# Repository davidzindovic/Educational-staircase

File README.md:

# Musical stairs with video effects
This project was constructed for use on the Faculty of Education, University of Ljubljana. The goal was to create attachable hardware to put onto an existing staircase (covering half the surface) with 2 turns and 25 steps.
Input data is processed by an ESP32, musical effects are played from an SD card with the help od MP3-TF player and visual effects are displayed on a projection/ screen via Raspberry Pi.
Data is transmitted from the ESP32 to RPI via Bluetooth.

# Hardware
- ESP32
- MP3-TF player module
- Mux 4051
- Raspberry Pi 5

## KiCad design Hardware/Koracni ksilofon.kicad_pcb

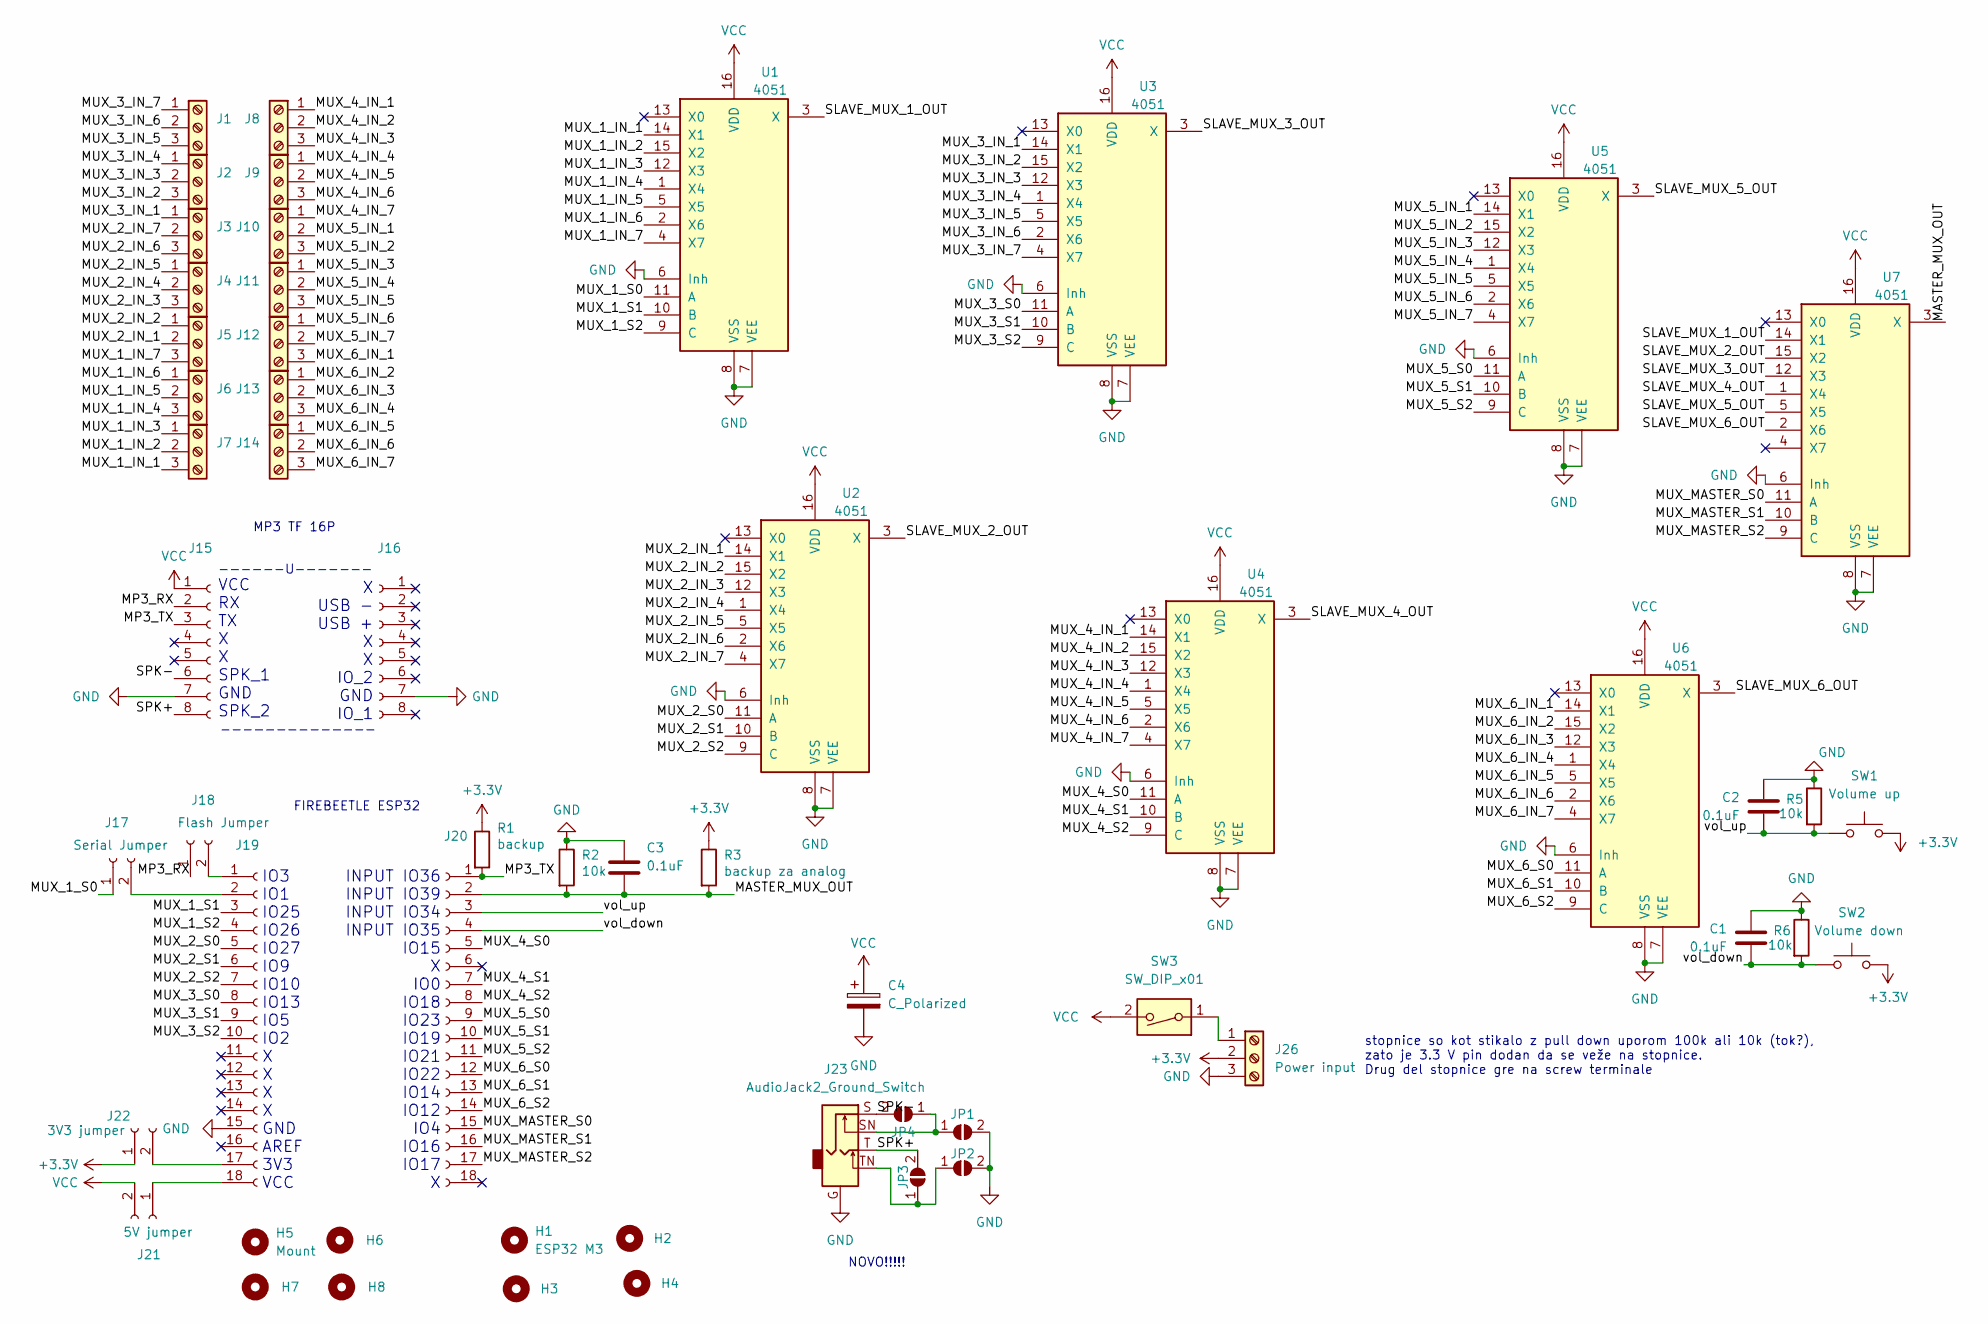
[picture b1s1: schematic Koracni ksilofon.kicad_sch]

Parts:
C1, C2, C3: 0.1uF; C_Disc_D3.4mm_W2.1mm_P2.50mm
C4: C_Polarized; CP_Radial_D5.0mm_P2.50mm
H1, H2, H3, H4: ESP32 M3; M3 luknja
H5, H6, H7, H8: Mount; MountingHole_3.2mm_M3
J1, J2, J3, J4, J5, J6, J7, J8, J9, J10, J11, J12, J13, J14: Screw_Terminal_01x03; TerminalBlock_bornier-3_P5.08mm
J15, J16: Conn_01x08_Socket; PinSocket_1x08_P2.54mm_Vertical
J17: Serial Jumper; PinHeader_1x02_P2.54mm_Vertical
J18: Flash Jumper; PinHeader_1x02_P2.54mm_Vertical
J19, J20: Conn_01x18_Socket; PinSocket_1x18_P2.54mm_Vertical
J21: 5V jumper; PinHeader_1x02_P2.54mm_Vertical
J22: 3V3 jumper; PinHeader_1x02_P2.54mm_Vertical
J23: AudioJack2_Ground_Switch; Audio jack connector
J26: Power input; TerminalBlock_bornier-3_P5.08mm
JP1, JP2, JP3, JP4: SolderJumper_2_Open; SolderJumper-2_P1.3mm_Open_TrianglePad1.0x1.5mm
R1: backup; R_Axial_DIN0207_L6.3mm_D2.5mm_P7.62mm_Horizontal
R2, R5, R6: 10k; R_Axial_DIN0207_L6.3mm_D2.5mm_P7.62mm_Horizontal
R3: backup za analog; R_Axial_DIN0207_L6.3mm_D2.5mm_P7.62mm_Horizontal
SW1: Volume up; PinHeader_1x02_P2.54mm_Vertical
SW2: Volume down; PinHeader_1x02_P2.54mm_Vertical
SW3: SW_DIP_x01; PinHeader_1x02_P2.54mm_Vertical
U1, U2, U3, U4, U5, U6, U7: 4051; DIP-16_W7.62mm

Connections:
+3.3V: J22.1, J26.2, R1.1, R3.1, SW1.2, SW2.2
/MASTER_MUX_OUT: C3.2, J20.2, R2.2, R3.2, U7.3 (X)
/MP3_RX: J15.2, J18.1
/MP3_TX: J15.3, J20.1, R1.2
/MUX_1_IN_1: J7.3, U1.14 (X1)
/MUX_1_IN_2: J7.2, U1.15 (X2)
/MUX_1_IN_3: J7.1, U1.12 (X3)
/MUX_1_IN_4: J6.3, U1.1 (X4)
/MUX_1_IN_5: J6.2, U1.5 (X5)
/MUX_1_IN_6: J6.1, U1.2 (X6)
/MUX_1_IN_7: J5.3, U1.4 (X7)
/MUX_1_S0: J17.1, U1.11 (A)
/MUX_1_S1: J19.3, U1.10 (B)
/MUX_1_S2: J19.4, U1.9 (C)
/MUX_2_IN_1: J5.2, U2.14 (X1)
/MUX_2_IN_2: J5.1, U2.15 (X2)
/MUX_2_IN_3: J4.3, U2.12 (X3)
/MUX_2_IN_4: J4.2, U2.1 (X4)
/MUX_2_IN_5: J4.1, U2.5 (X5)
/MUX_2_IN_6: J3.3, U2.2 (X6)
/MUX_2_IN_7: J3.2, U2.4 (X7)
/MUX_2_S0: J19.5, U2.11 (A)
/MUX_2_S1: J19.6, U2.10 (B)
/MUX_2_S2: J19.7, U2.9 (C)
/MUX_3_IN_1: J3.1, U3.14 (X1)
/MUX_3_IN_2: J2.3, U3.15 (X2)
/MUX_3_IN_3: J2.2, U3.12 (X3)
/MUX_3_IN_4: J2.1, U3.1 (X4)
/MUX_3_IN_5: J1.3, U3.5 (X5)
/MUX_3_IN_6: J1.2, U3.2 (X6)
/MUX_3_IN_7: J1.1, U3.4 (X7)
/MUX_3_S0: J19.8, U3.11 (A)
/MUX_3_S1: J19.9, U3.10 (B)
/MUX_3_S2: J19.10, U3.9 (C)
/MUX_4_IN_1: J8.1, U4.14 (X1)
/MUX_4_IN_2: J8.2, U4.15 (X2)
/MUX_4_IN_3: J8.3, U4.12 (X3)
/MUX_4_IN_4: J9.1, U4.1 (X4)
/MUX_4_IN_5: J9.2, U4.5 (X5)
/MUX_4_IN_6: J9.3, U4.2 (X6)
/MUX_4_IN_7: J10.1, U4.4 (X7)
/MUX_4_S0: J20.5, U4.11 (A)
/MUX_4_S1: J20.7, U4.10 (B)
/MUX_4_S2: J20.8, U4.9 (C)
/MUX_5_IN_1: J10.2, U5.14 (X1)
/MUX_5_IN_2: J10.3, U5.15 (X2)
/MUX_5_IN_3: J11.1, U5.12 (X3)
/MUX_5_IN_4: J11.2, U5.1 (X4)
/MUX_5_IN_5: J11.3, U5.5 (X5)
/MUX_5_IN_6: J12.1, U5.2 (X6)
/MUX_5_IN_7: J12.2, U5.4 (X7)
/MUX_5_S0: J20.9, U5.11 (A)
/MUX_5_S1: J20.10, U5.10 (B)
/MUX_5_S2: J20.11, U5.9 (C)
/MUX_6_IN_1: J12.3, U6.14 (X1)
/MUX_6_IN_2: J13.1, U6.15 (X2)
/MUX_6_IN_3: J13.2, U6.12 (X3)
/MUX_6_IN_4: J13.3, U6.1 (X4)
/MUX_6_IN_5: J14.1, U6.5 (X5)
/MUX_6_IN_6: J14.2, U6.2 (X6)
/MUX_6_IN_7: J14.3, U6.4 (X7)
/MUX_6_S0: J20.12, U6.11 (A)
/MUX_6_S1: J20.13, U6.10 (B)
/MUX_6_S2: J20.14, U6.9 (C)
/MUX_MASTER_S0: J20.15, U7.11 (A)
/MUX_MASTER_S1: J20.16, U7.10 (B)
/MUX_MASTER_S2: J20.17, U7.9 (C)
/SLAVE_MUX_1_OUT: U1.3 (X), U7.14 (X1)
/SLAVE_MUX_2_OUT: U2.3 (X), U7.15 (X2)
/SLAVE_MUX_3_OUT: U3.3 (X), U7.12 (X3)
/SLAVE_MUX_4_OUT: U4.3 (X), U7.1 (X4)
/SLAVE_MUX_5_OUT: U5.3 (X), U7.5 (X5)
/SLAVE_MUX_6_OUT: U6.3 (X), U7.2 (X6)
/SPK+: J15.8, J23.T, JP3.2 (B)
/SPK-: J15.6, J23.S, JP4.2 (B)
/vol_down: C1.2, J20.4, R6.2, SW2.1
/vol_up: C2.2, J20.3, R5.2, SW1.1
GND: C1.1, C2.1, C3.1, C4.2, J15.7, J16.7, J19.15, J23.G, J26.3, JP1.2 (B), JP2.2 (B), R2.1, R5.1, R6.1, U1.6 (Inh), U1.7 (VEE), U1.8 (VSS), U2.6 (Inh), U2.7 (VEE), U2.8 (VSS), U3.6 (Inh), U3.7 (VEE), U3.8 (VSS), U4.6 (Inh), U4.7 (VEE), U4.8 (VSS), U5.6 (Inh), U5.7 (VEE), U5.8 (VSS), U6.6 (Inh), U6.7 (VEE), U6.8 (VSS), U7.6 (Inh), U7.7 (VEE), U7.8 (VSS)
unnamed: J17.2, J19.2
unnamed: J18.2, J19.1
unnamed: J19.17, J22.2
unnamed: J19.18, J21.1
unnamed: J26.1, SW3.1
unnamed: J23.SN, JP1.1 (A), JP4.1 (A)
unnamed: J23.TN, JP2.1 (A), JP3.1 (A)
VCC: C4.1, J15.1, J21.2, SW3.2, U1.16 (VDD), U2.16 (VDD), U3.16 (VDD), U4.16 (VDD), U5.16 (VDD), U6.16 (VDD), U7.16 (VDD)

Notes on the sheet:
stopnice so kot stikalo z pull down uporom 100k ali 10k (tok?), zato je 3.3 V pin dodan da se veže na stopnice. Drug del stopnice gre na screw terminale
--------------
X USB - USB + X X IO_2 GND IO_1
NOVO!!!!!
FIREBEETLE ESP32
INPUT IO36 INPUT IO39 INPUT IO34 INPUT IO35 IO15 X IO0 IO18 IO23 IO19 IO21 IO22 IO14 IO12 IO4 IO16 IO17 X
IO3 IO1 IO25 IO26 IO27 IO9 IO10 IO13 IO5 IO2 X X X X GND AREF 3V3 VCC
MP3 TF 16P
VCC RX TX X X SPK_1 GND SPK_2
------U-------

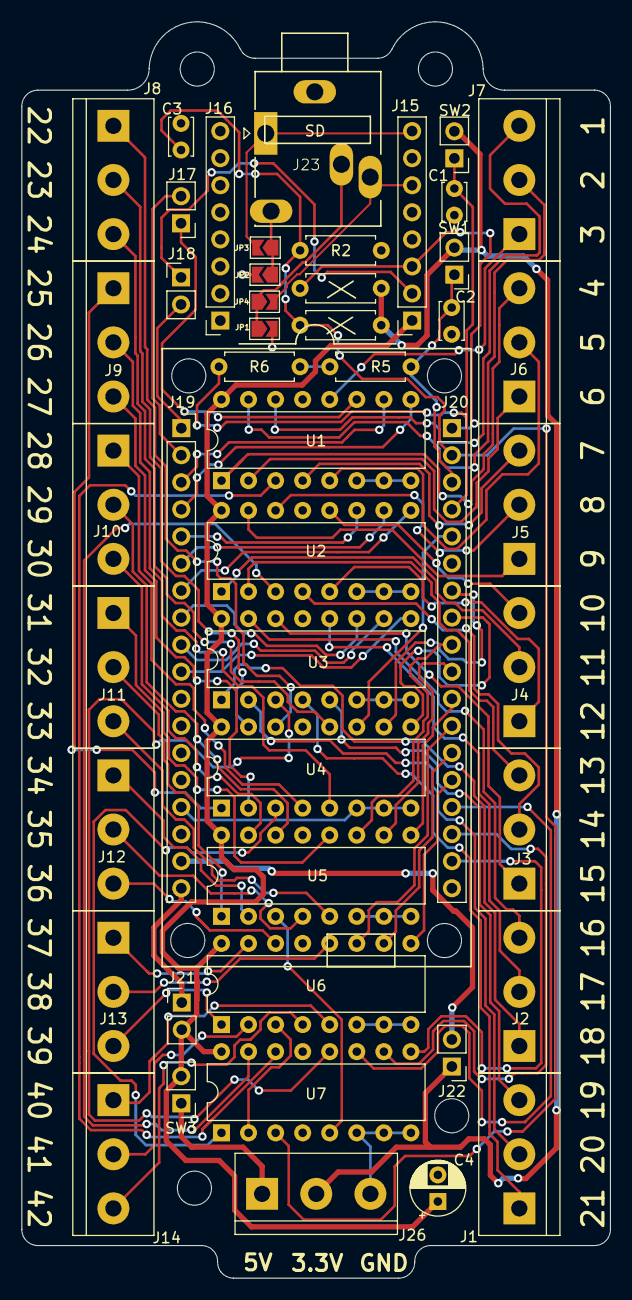
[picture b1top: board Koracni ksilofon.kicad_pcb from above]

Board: 2 copper layers, 55.2 x 117.9 mm, 55 parts (0 on the bottom side), 86 nets.

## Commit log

2025-06-11 Rename Libraries/CD74HC4051E_lib.zip to Libraries/ESP32/CD74HC4051E_lib.zip
2025-06-11 Rename Libraries/DFPlayerMini_Fast-master.zip to Libraries/ESP32/DFPlayerMini_Fast-master.zip
2025-06-11 Rename installation_notes.md to Libraries/installation_notes.md
2025-06-11 Rename shema koracni ksilofon.PNG to PCB/shema koracni ksilofon.PNG
2025-06-11 Rename stopnice_esp32 to Code/ESP32_main.ino
2025-06-11 Rename koncna.py to Code/RPI_main
2025-06-11 Rename stopnica_mere.png to Images/Staircase_dimensions.png
2025-06-11 Rename stopnica.png to Images/star.png
2025-06-11 Rename star.png to part_of_staircase.png
2025-06-12 Rename RPI_main to RPI_main.py
2025-07-02 Rename RPI_commands.md to RPI_commands.md
2025-07-09 Rename Technical drawing.JPG to Technical_drawing.JPG
2025-07-09 Rename Libraries/README.md to Code/Libraries/README.md
2025-07-09 Rename Libraries/ESP32/CD74HC4051E_lib.zip to Code/Libraries/ESP32/CD74HC4051E_lib.zip
2025-07-09 Rename Libraries/ESP32/DFPlayerMini_Fast-master.zip to Code/Libraries/ESP32/DFPlayerMini_Fast-master.zip
2025-07-09 Rename Libraries/installation_notes.md to Code/Libraries/installation_notes.md
2025-07-09 Rename Orodja_za_razvoj/README.md to Code/Developer_tools/README.md
2025-07-09 Rename Orodja_za_razvoj/Okolje_za_pripravo.py to Code/Developer_tools/Okolje_za_pripravo.py
2025-07-09 Rename Orodja_za_razvoj/RPI_commands.md to Code/Developer_tools/RPI_commands.md
2025-07-09 Rename Orodja_za_razvoj/Program_exe/Okolje_za_pripravo.py to Code/Developer_tools/exe/Okolje_za_pripravo.py
2025-07-09 Rename Orodja_za_razvoj/Program_exe/UL_PEF_logo.png to Code/Developer_tools/exe/UL_PEF_logo.png
2025-07-09 Rename Orodja_za_razvoj/Program_exe/icon.ico to Code/Developer_tools/exe/icon.ico
2025-07-09 Rename Orodja_za_razvoj/Program_exe/usb_monitor.py to Code/Developer_tools/exe/usb_monitor.py
2025-07-09 Rename shema koracni ksilofon.PNG to Schematic.PNG
2025-07-09 Rename Koracni_ksilofon.png to PCB_render.png
2025-07-14 Rename RPI_main.py to Desktop_RPI_main.py
2026-05-22 Rename patches.txt to Code/Developer_tools/patches.md
